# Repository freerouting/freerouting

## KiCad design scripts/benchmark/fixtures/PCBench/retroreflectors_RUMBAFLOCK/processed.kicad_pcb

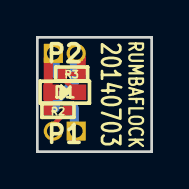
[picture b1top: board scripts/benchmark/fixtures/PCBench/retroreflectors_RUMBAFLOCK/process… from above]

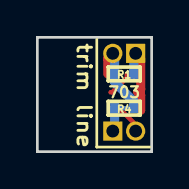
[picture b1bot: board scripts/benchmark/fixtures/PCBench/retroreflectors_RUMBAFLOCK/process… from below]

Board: 2 copper layers, 6.3 x 6.4 mm, 7 parts (2 on the bottom side), 5 nets.

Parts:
D1: PIN; GSG-0603D
P1: INPUT; GSG-50MIL-HEADER-1x2-TH
P2: ANTENNA; GSG-50MIL-HEADER-1x2-TH
R1: DNP; GSG-0402
R2: 10k; GSG-0402
R3, R4: 0; GSG-0402-SHORT-10MIL

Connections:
GND: P2.2, R1.2, R3.1, R4.1
unnamed: P1.1, R4.2
unnamed: P1.2, R2.1
unnamed: D1.2, R3.2
unnamed: D1.1, P2.1, R1.1, R2.2

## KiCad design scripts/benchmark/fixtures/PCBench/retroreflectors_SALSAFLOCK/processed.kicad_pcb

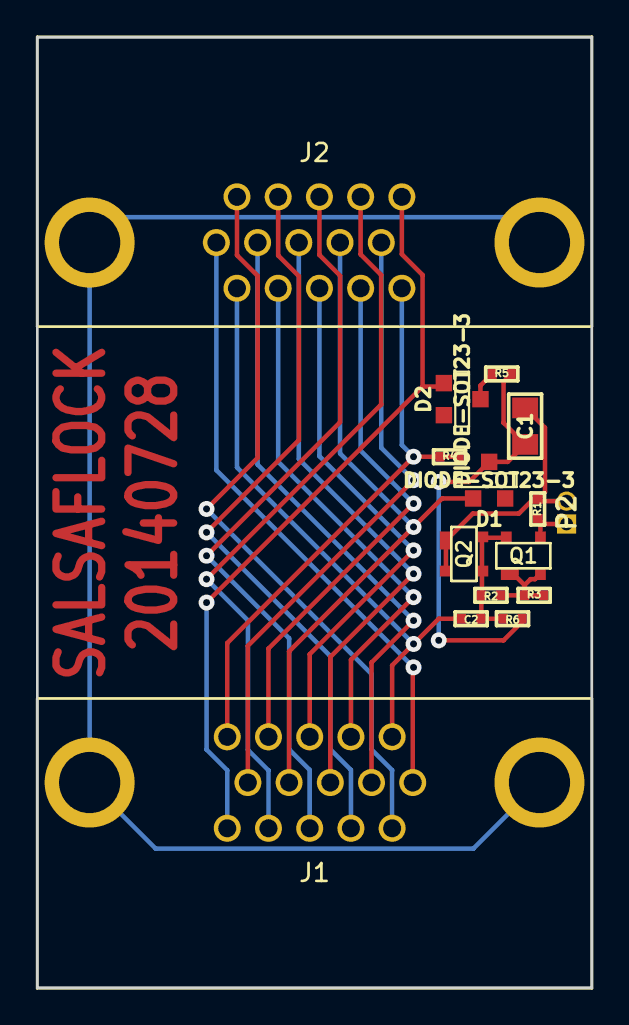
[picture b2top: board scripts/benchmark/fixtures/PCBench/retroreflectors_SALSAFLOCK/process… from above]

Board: 2 copper layers, 30.8 x 52.8 mm, 15 parts (0 on the bottom side), 22 nets.

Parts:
C1: 22uF; GSG-0805
C2: 1uF; GSG-0402
D1, D2: DIODE-SOT23-3; GSG-SOT23-3
J1, J2: DB15-VGA; GSG-DB15-VGA
P2: ANTENNA; GSG-50MIL-HEADER-1x2-TH
Q1, Q2: MOSFET_N; GSG-SOT143B-GDS
R1: DNP; GSG-0402
R2, R5, R6: 10k; GSG-0402
R3, R4: 0; GSG-0402-SHORT-10MIL

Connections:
/DRAIN: P2.1, Q1.D, R1.1
/GATE: C2.2, Q1.G, Q2.D, Q2.G, R2.1, R6.1
/KEY: D1.1, J1.9, J2.9
/RED: C2.1, J1.1, J2.1
/SCL: D2.1, J1.15, J2.15
/SHIELD: J1.0, J2.0
/SOURCE: Q1.B, Q1.S, R2.2, R3.2
/VGAGND: J1.5, J2.5, R4.2
GND: C1.1, P2.2, Q2.B, Q2.S, R1.2
unnamed: J1.10, J2.10
unnamed: J1.7, J2.7
unnamed: J1.2, J2.2
unnamed: J1.3, J2.3
unnamed: J1.4, J2.4
unnamed: J1.6, J2.6
unnamed: J1.8, J2.8
unnamed: J1.11, J2.11
unnamed: J1.12, J2.12
unnamed: J1.13, J2.13
unnamed: J1.14, J2.14
unnamed: D2.3, R5.2
unnamed: C1.2, D1.3, R5.1, R6.2

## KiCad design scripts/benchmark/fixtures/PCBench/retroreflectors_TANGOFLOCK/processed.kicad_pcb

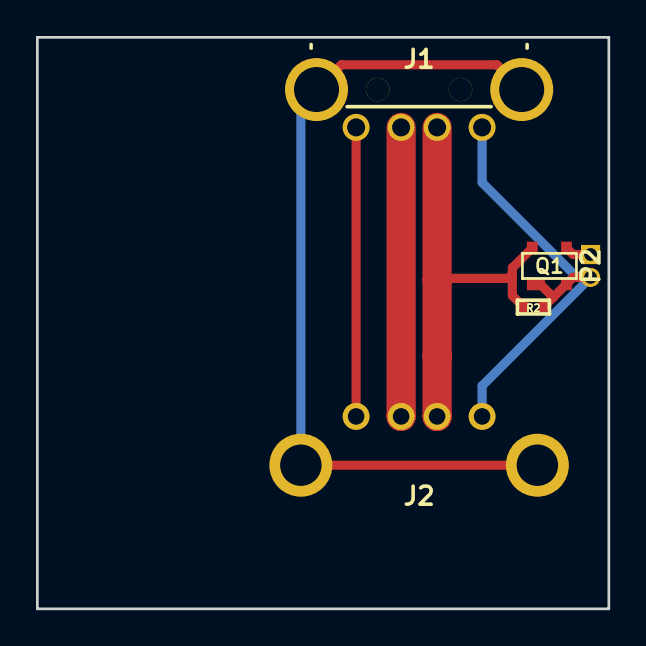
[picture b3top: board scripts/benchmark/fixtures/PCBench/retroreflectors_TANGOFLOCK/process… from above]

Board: 2 copper layers, 31.8 x 31.8 mm, 5 parts (0 on the bottom side), 6 nets.

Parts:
J1: USB-DEVICE-SHIELD; GSG-USB-A-1001-010-01001-SHIELD
J2: USB-DEVICE-SHIELD; GSG-USB-A1HSW6
P2: ANTENNA; GSG-50MIL-HEADER-1x2-TH
Q1: MOSFET_N; GSG-SOT143B-GDS
R2: 10k; GSG-0402

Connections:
/DRAIN: P2.1, Q1.D
/GATE: J1.3, J2.3, Q1.G, R2.1
/SHIELD: J1.5, J2.5
GND: J1.4, J2.4, P2.2, Q1.B, Q1.S, R2.2
unnamed: J1.1, J2.1
unnamed: J1.2, J2.2
